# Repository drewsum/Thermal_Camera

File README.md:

# Thermal_Camera
DIY Thermal Camera - Drew Maatman and Michael Laffin

## Hardware:
### KiCad Project:
\Thermal_Camera\rev_a\hdw\Thermal_Camera
Made in KiCad version 8.0.5
PIC32MZ DA Grphics MCU
FLIR Lepton 3.5 Thermal Imagery Sensor
PIC32MZ DA is programmed with firmware via PICKIT4 Header (J1501)
PIC32MZ DA can be held in reset by pressing SW1501 or by inserting jumper across J1502
USB Hub can be reset by pressing SW2501
SPI FLASH can be programmed via J2002

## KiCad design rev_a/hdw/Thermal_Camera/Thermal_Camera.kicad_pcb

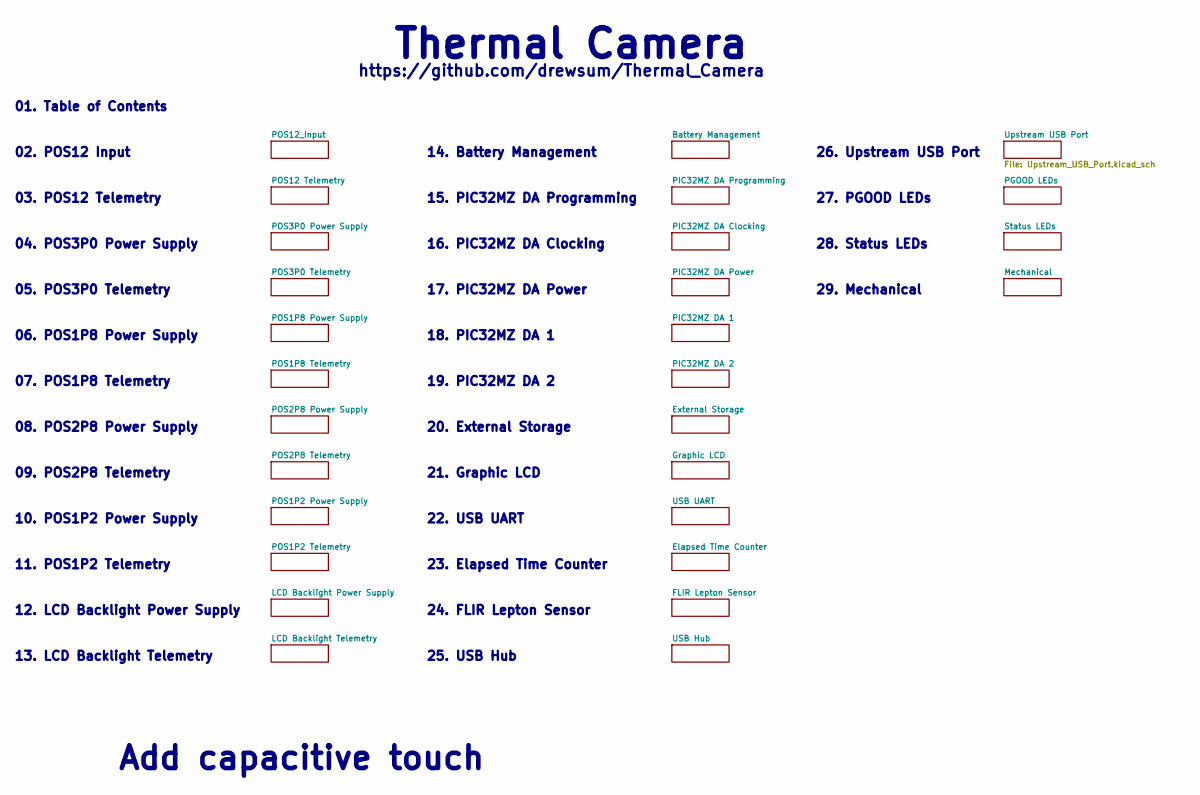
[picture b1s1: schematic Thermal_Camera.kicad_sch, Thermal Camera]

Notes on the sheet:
08. POS2P8 Power Supply
12. LCD Backlight Power Supply
26. Upstream USB Port
15. PIC32MZ DA Programming
28. Status LEDs
05. POS3P0 Telemetry
27. PGOOD LEDs
02. POS12 Input
25. USB Hub
22. USB UART
01. Table of Contents
23. Elapsed Time Counter
20. External Storage
Thermal Camera
24. FLIR Lepton Sensor
11. POS1P2 Telemetry
18. PIC32MZ DA 1
03. POS12 Telemetry
13. LCD Backlight Telemetry
19. PIC32MZ DA 2
14. Battery Management
10. POS1P2 Power Supply
Add capacitive touch
17. PIC32MZ DA Power
https://github.com/drewsum/Thermal_Camera
29. Mechanical
09. POS2P8 Telemetry
07. POS1P8 Telemetry
04. POS3P0 Power Supply
16. PIC32MZ DA Clocking
06. POS1P8 Power Supply
21. Graphic LCD

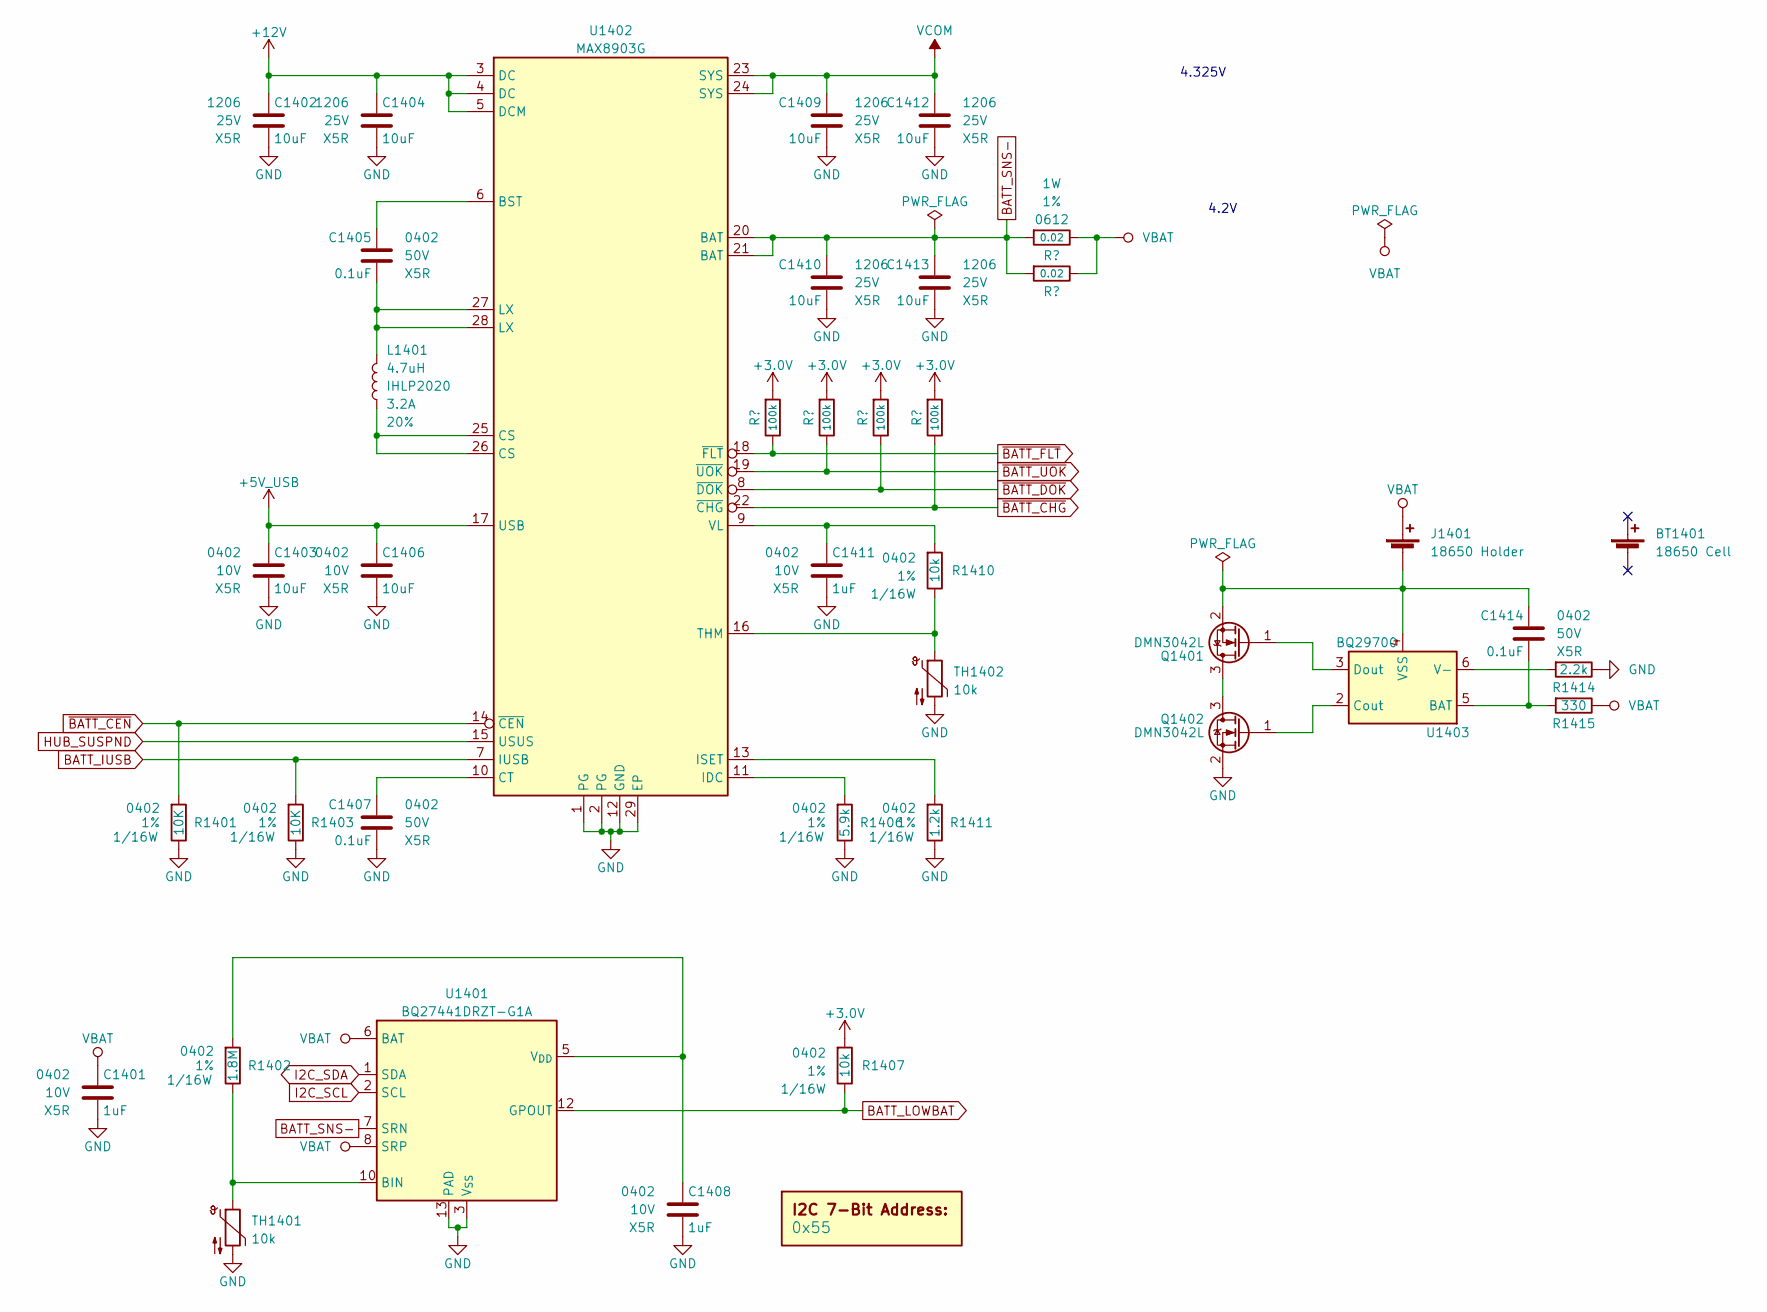
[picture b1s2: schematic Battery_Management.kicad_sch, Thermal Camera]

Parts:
BT1401: 18650 Cell; Digi-Key PN 1568-1488-ND
C1401, C1408, C1411: 1uF; C_0402; Voltage 10V; Digi-Key PN 311-1439-1-ND
C1402, C1404, C1409, C1410, C1412, C1413: 10uF; C_1206; Voltage 25V; Digi-Key PN 399-8153-1-ND
C1403, C1406: 10uF; C_0402; Voltage 10V; Digi-Key PN 490-GRM155R61A106ME11DCT-ND
C1405, C1407, C1414: 0.1uF; C_0402; Voltage 50V; Digi-Key PN 490-10697-1-ND
DOC1401: 0x55
J1401: 18650 Holder; BatteryHolder_MPD_BH-18650-PC2; Digi-Key PN BK-18650-PC2-ND
L1401: 4.7uH; L_Vishay_IHLP-2020; Tolerance 20%; Digi-Key PN 541-1222-1-ND
Q1401, Q1402: DMN3042L; SOT-23; Digi-Key PN DMN3042L-7DICT-ND
R1401, R1403: 10K; R_0402; Tolerance 1%; Digi-Key PN RMCF0402FT10K0CT-ND
R1402: 1.8M; R_0402; Tolerance 1%; Digi-Key PN RMCF0402FT1M80CT-ND
R1404, R1405, R1408, R1409: 100k; R_0402; Tolerance 1%; Digi-Key PN RMCF0402FT100KCT-ND
R1406: 5.9k; R_0402; Tolerance 1%; Digi-Key PN RMCF0402FT5K90CT-ND
R1407, R1410: 10k; R_0402; Tolerance 1%; Digi-Key PN RMCF0402FT10K0CT-ND
R1411: 1.2k; R_0402; Tolerance 1%; Digi-Key PN RMCF0402FT1K20CT-ND
R1412, R1413: 0.02; R_0612; Tolerance 1%; Digi-Key PN P16010CT-ND
R1414: 2.2k; R_0402; Tolerance 1%; Digi-Key PN RMCF0402FT2K20CT-ND
R1415: 330; R_0402; Tolerance 1%; Digi-Key PN RMCF0402FT330RCT-ND
TH1401, TH1402: 10k; R_0402; Digi-Key PN 445-174911-1-ND
U1401: BQ27441DRZT-G1A; Texas_S-PDSO-N12; Digi-Key PN 296-37271-1-ND
U1402: MAX8903G; QFN-28-1EP_4x4mm_P0.4mm_EP2.6x2.6mm; Digi-Key PN MAX8903GETI+-ND
U1403: BQ29700; WSON-6_1.5x1.5mm_P0.5mm; Digi-Key PN 296-43985-1-ND

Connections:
+3.0V: R1404.1, R1405.1, R1407.1, R1408.1, R1409.1; also elsewhere on the board
+5V_USB: C1403.1, C1406.1, U1402.17 (USB); also elsewhere on the board
+12V: C1402.1, C1404.1, U1402.3 (DC), U1402.4 (DC), U1402.5 (DCM); also elsewhere on the board
BATT_IUSB: R1403.1, U1402.7 (IUSB); also elsewhere on the board
BATT_LOWBAT: R1407.2, U1401.12 (GPOUT); also elsewhere on the board
BATT_SNS-: C1410.1, C1413.1, R1412.1, R1413.1, U1401.7 (SRN), U1402.20 (BAT), U1402.21 (BAT)
GND: C1401.2, C1402.2, C1403.2, C1404.2, C1406.2, C1407.2, C1408.2, C1409.2, C1410.2, C1411.2, C1412.2, C1413.2, Q1402.2 (S), R1401.2, R1403.2, R1406.2, R1411.2, R1414.2, TH1401.2, TH1402.2, U1401.3 (V_{SS}), U1401.13 (PAD), U1402.1 (PG), U1402.2 (PG), U1402.12 (GND), U1402.29 (EP); also elsewhere on the board
HUB_SUSPND: U1402.15 (USUS); also elsewhere on the board
I2C_SCL: U1401.2 (SCL); also elsewhere on the board
I2C_SDA: U1401.1 (SDA); also elsewhere on the board
unnamed: C1405.2, L1401.2, U1402.27 (LX), U1402.28 (LX)
unnamed: C1414.1, J1401.2 (-), Q1401.2 (S), U1403.4 (VSS)
unnamed: L1401.1, U1402.25 (CS), U1402.26 (CS)
unnamed: Q1401.3 (D), Q1402.3 (D)
unnamed: Q1401.1 (G), U1403.3 (Dout)
unnamed: Q1402.1 (G), U1403.2 (Cout)
unnamed: R1402.2, TH1401.1, U1401.10 (BIN)
unnamed: C1408.1, R1402.1, U1401.5 (V_{DD})
unnamed: C1405.1, U1402.6 (BST)
unnamed: C1407.1, U1402.10 (CT)
unnamed: R1406.1, U1402.11 (IDC)
unnamed: R1411.1, U1402.13 (ISET)
unnamed: R1410.2, TH1402.1, U1402.16 (THM)
unnamed: C1411.1, R1410.1, U1402.9 (VL)
unnamed: C1414.2, R1415.1, U1403.5 (BAT)
unnamed: R1414.1, U1403.6 (V-)
VBAT: C1401.1, J1401.1 (+), R1412.2, R1413.2, R1415.2, U1401.6 (BAT), U1401.8 (SRP)
VCOM: C1409.1, C1412.1, U1402.23 (SYS), U1402.24 (SYS); also elsewhere on the board
~BATT_CEN: R1401.1, U1402.14 (~CEN); also elsewhere on the board
~BATT_CHG: R1409.2, U1402.22 (~CHG); also elsewhere on the board
~BATT_DOK: R1408.2, U1402.8 (~DOK); also elsewhere on the board
~BATT_FLT: R1404.2, U1402.18 (~FLT); also elsewhere on the board
~BATT_UOK: R1405.2, U1402.19 (~UOK); also elsewhere on the board

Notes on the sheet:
4.325V
4.2V

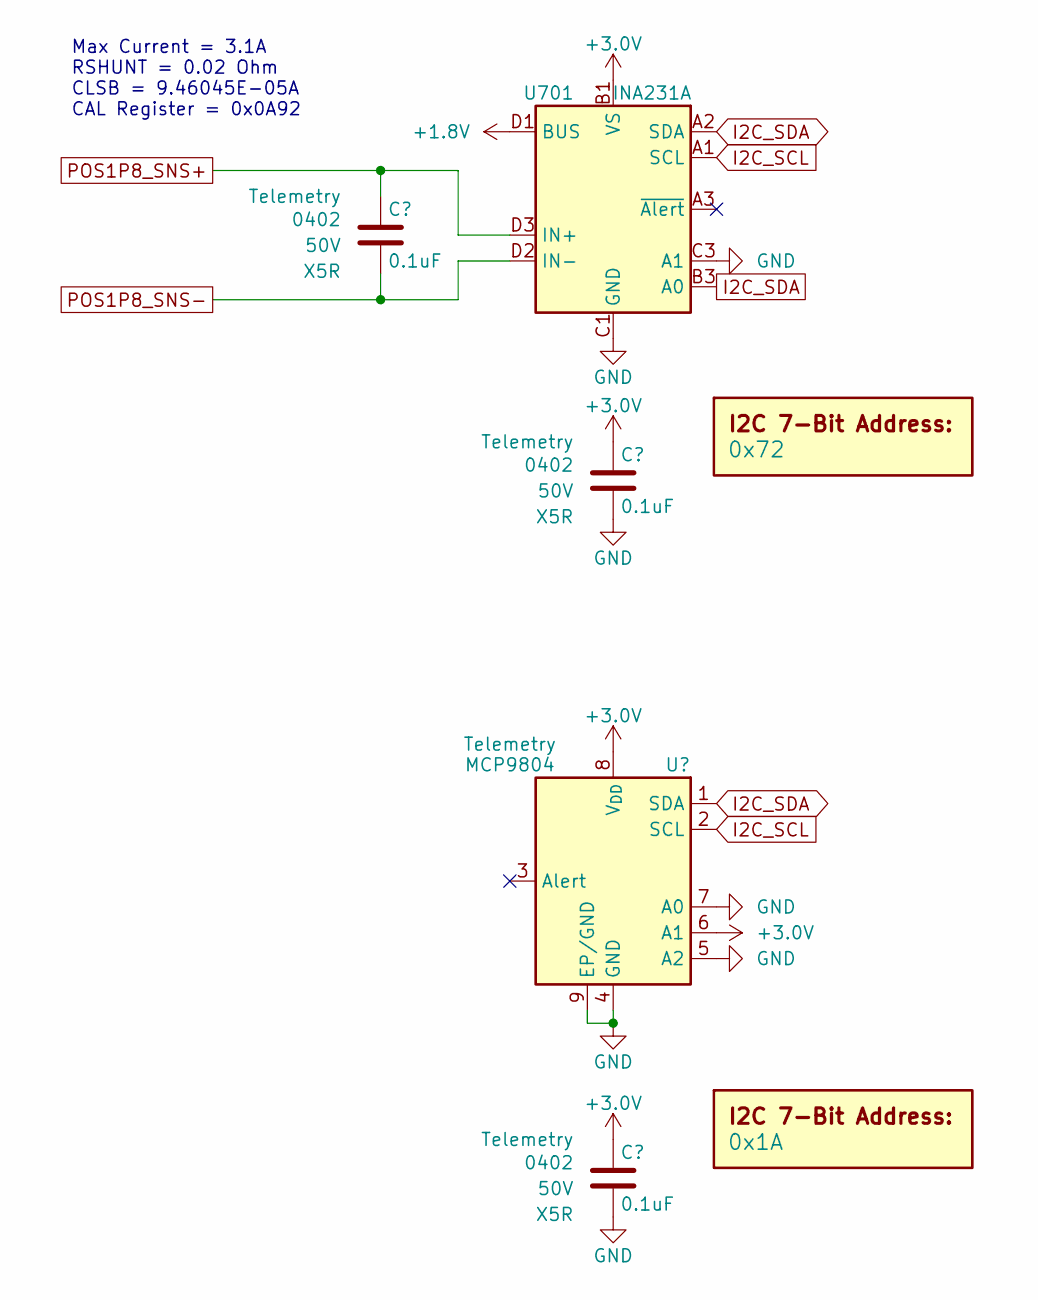
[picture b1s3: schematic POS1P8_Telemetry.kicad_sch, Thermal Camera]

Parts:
C701, C702, C703: 0.1uF; C_0402; Voltage 50V; Digi-Key PN 490-10697-1-ND
DOC701: 0x72
DOC702: 0x1A
U701: INA231A; Texas_DSBGA-12_1.65x1.39mm_Layout3x4_P0.4mm; Digi-Key PN 296-41263-1-ND
U702: MCP9804; DFN-8-1EP_3x2mm_P0.5mm_EP1.3x1.5mm; Digi-Key PN MCP9804T-E/MCCT-ND

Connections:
+1.8V: U701.D1 (BUS); also elsewhere on the board
+3.0V: C702.1, C703.1, U701.B1 (VS), U702.6 (A1), U702.8 (V_{DD}); also elsewhere on the board
GND: C702.2, C703.2, U701.C1 (GND), U701.C3 (A1), U702.4 (GND), U702.5 (A2), U702.7 (A0), U702.9 (EP/GND); also elsewhere on the board
I2C_SCL: U701.A1 (SCL), U702.2 (SCL); also elsewhere on the board
I2C_SDA: U701.A2 (SDA), U701.B3 (A0), U702.1 (SDA); also elsewhere on the board
POS1P8_SNS+: C701.1, U701.D3 (IN+); also elsewhere on the board
POS1P8_SNS-: C701.2, U701.D2 (IN-); also elsewhere on the board

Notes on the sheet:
Max Current = 3.1A RSHUNT = 0.02 Ohm CLSB = 9.46045E-05A CAL Register = 0x0A92

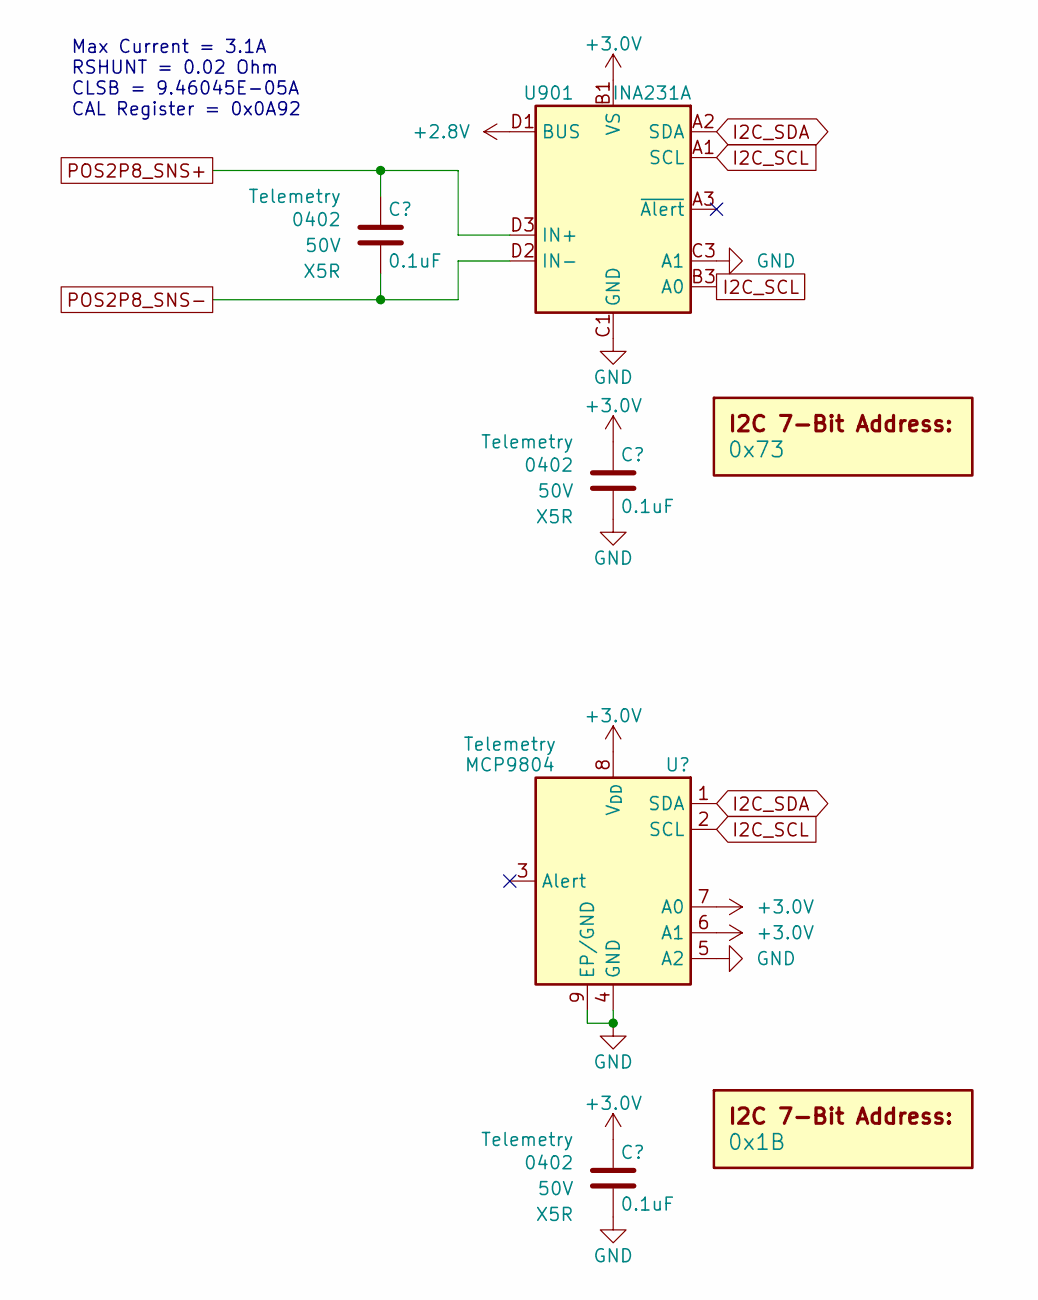
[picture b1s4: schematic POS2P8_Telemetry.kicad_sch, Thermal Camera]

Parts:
C901, C902, C903: 0.1uF; C_0402; Voltage 50V; Digi-Key PN 490-10697-1-ND
DOC901: 0x73
DOC902: 0x1B
U901: INA231A; Texas_DSBGA-12_1.65x1.39mm_Layout3x4_P0.4mm; Digi-Key PN 296-41263-1-ND
U902: MCP9804; DFN-8-1EP_3x2mm_P0.5mm_EP1.3x1.5mm; Digi-Key PN MCP9804T-E/MCCT-ND

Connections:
+2.8V: U901.D1 (BUS); also elsewhere on the board
+3.0V: C902.1, C903.1, U901.B1 (VS), U902.6 (A1), U902.7 (A0), U902.8 (V_{DD}); also elsewhere on the board
GND: C902.2, C903.2, U901.C1 (GND), U901.C3 (A1), U902.4 (GND), U902.5 (A2), U902.9 (EP/GND); also elsewhere on the board
I2C_SCL: U901.A1 (SCL), U901.B3 (A0), U902.2 (SCL); also elsewhere on the board
I2C_SDA: U901.A2 (SDA), U902.1 (SDA); also elsewhere on the board
POS2P8_SNS+: C901.1, U901.D3 (IN+); also elsewhere on the board
POS2P8_SNS-: C901.2, U901.D2 (IN-); also elsewhere on the board

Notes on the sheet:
Max Current = 3.1A RSHUNT = 0.02 Ohm CLSB = 9.46045E-05A CAL Register = 0x0A92

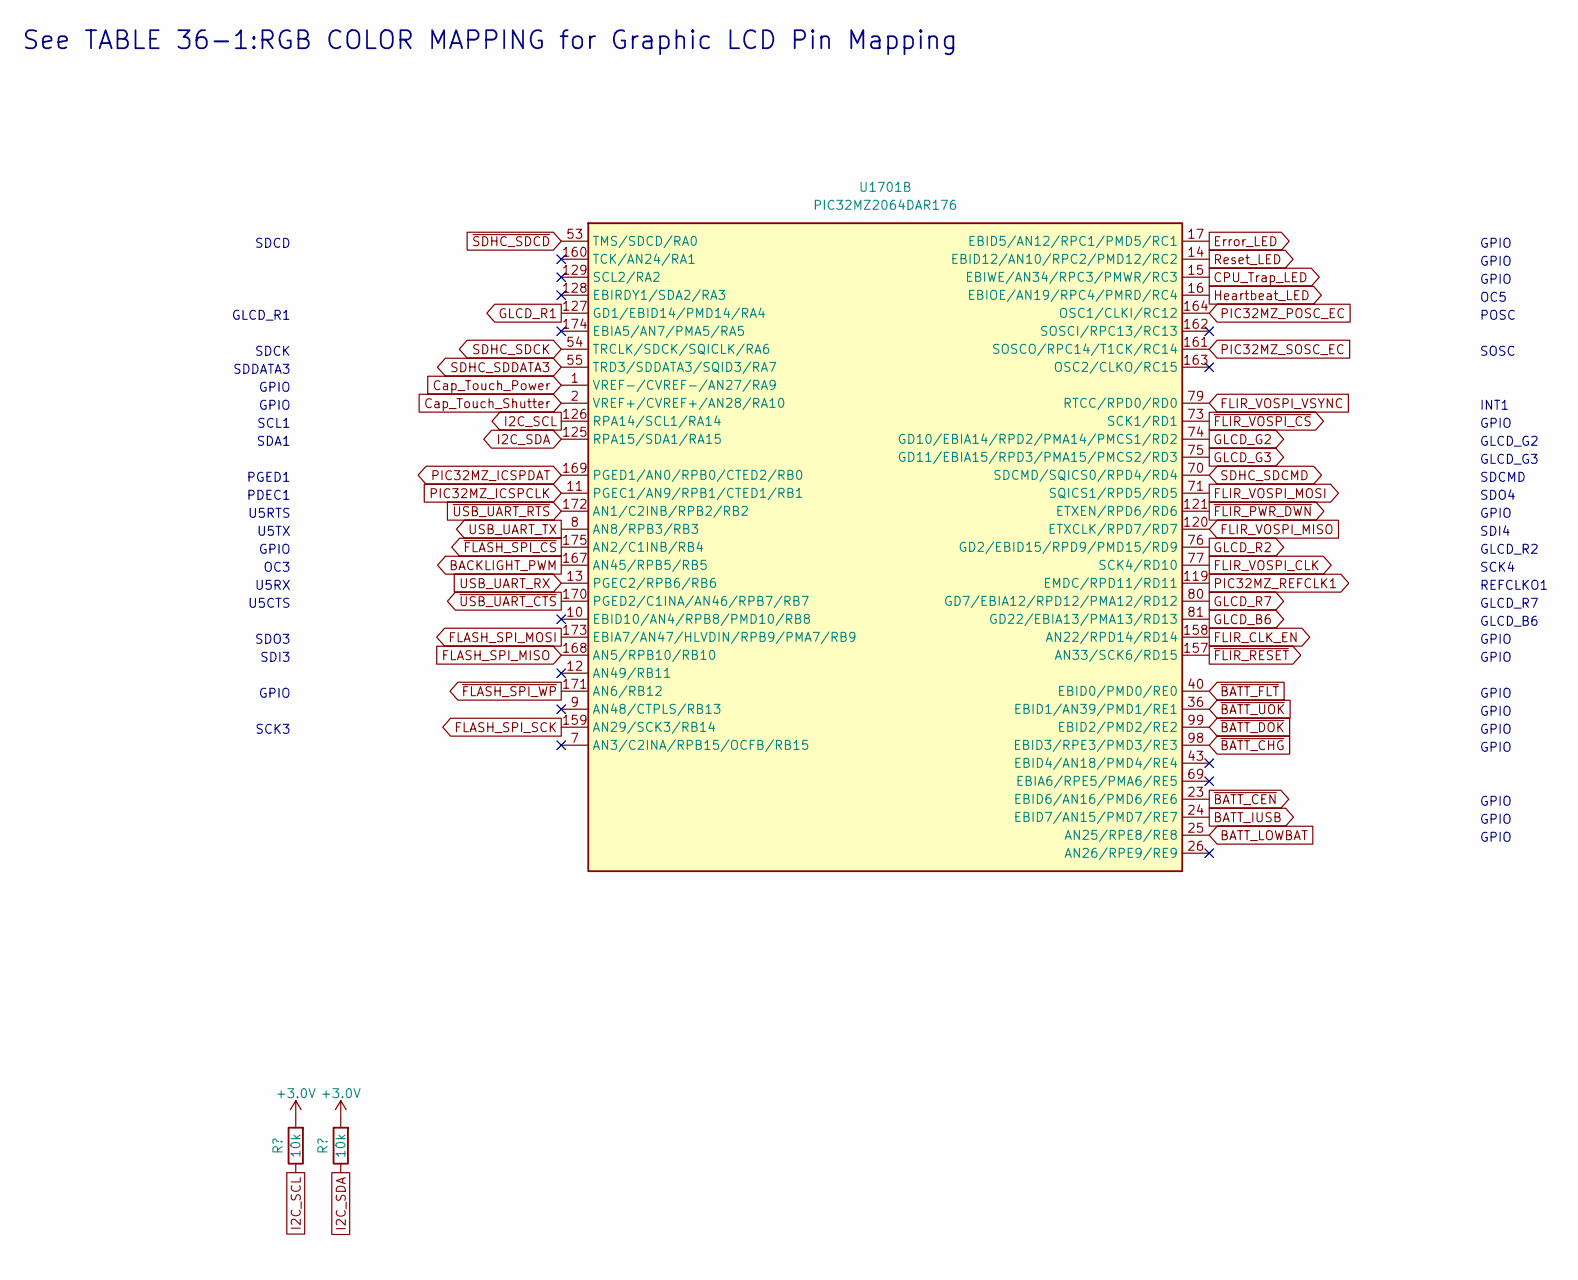
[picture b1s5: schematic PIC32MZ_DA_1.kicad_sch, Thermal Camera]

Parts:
R1801, R1802: 10k; R_0402; Tolerance 1%; Digi-Key PN RMCF0402FT10K0CT-ND
U1701: PIC32MZ2064DAR176; LQFP-176_20x20mm_P0.4mm_7p9x7p9mm_EP; Digi-Key PN PIC32MZ2064DAR176-I/2J-ND

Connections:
+3.0V: R1801.1, R1802.1; also elsewhere on the board
BACKLIGHT_PWM: U1701.167 (AN45/RPB5/RB5); also elsewhere on the board
BATT_IUSB: U1701.24 (EBID7/AN15/PMD7/RE7); also elsewhere on the board
BATT_LOWBAT: U1701.25 (AN25/RPE8/RE8); also elsewhere on the board
CPU_Trap_LED: U1701.15 (EBIWE/AN34/RPC3/PMWR/RC3); also elsewhere on the board
Cap_Touch_Power: U1701.1 (VREF-/CVREF-/AN27/RA9); also elsewhere on the board
Cap_Touch_Shutter: U1701.2 (VREF+/CVREF+/AN28/RA10); also elsewhere on the board
Error_LED: U1701.17 (EBID5/AN12/RPC1/PMD5/RC1); also elsewhere on the board
FLASH_SPI_MISO: U1701.168 (AN5/RPB10/RB10); also elsewhere on the board
FLASH_SPI_MOSI: U1701.173 (EBIA7/AN47/HLVDIN/RPB9/PMA7/RB9); also elsewhere on the board
FLASH_SPI_SCK: U1701.159 (AN29/SCK3/RB14); also elsewhere on the board
FLIR_CLK_EN: U1701.158 (AN22/RPD14/RD14); also elsewhere on the board
FLIR_VOSPI_CLK: U1701.77 (SCK4/RD10); also elsewhere on the board
FLIR_VOSPI_MISO: U1701.120 (ETXCLK/RPD7/RD7); also elsewhere on the board
FLIR_VOSPI_MOSI: U1701.71 (SQICS1/RPD5/RD5); also elsewhere on the board
FLIR_VOSPI_VSYNC: U1701.79 (RTCC/RPD0/RD0); also elsewhere on the board
GLCD_B6: U1701.81 (GD22/EBIA13/PMA13/RD13); also elsewhere on the board
GLCD_G2: U1701.74 (GD10/EBIA14/RPD2/PMA14/PMCS1/RD2); also elsewhere on the board
GLCD_G3: U1701.75 (GD11/EBIA15/RPD3/PMA15/PMCS2/RD3); also elsewhere on the board
GLCD_R1: U1701.127 (GD1/EBID14/PMD14/RA4); also elsewhere on the board
GLCD_R2: U1701.76 (GD2/EBID15/RPD9/PMD15/RD9); also elsewhere on the board
GLCD_R7: U1701.80 (GD7/EBIA12/RPD12/PMA12/RD12); also elsewhere on the board
Heartbeat_LED: U1701.16 (EBIOE/AN19/RPC4/PMRD/RC4); also elsewhere on the board
I2C_SCL: R1801.2, U1701.126 (RPA14/SCL1/RA14); also elsewhere on the board
I2C_SDA: R1802.2, U1701.125 (RPA15/SDA1/RA15); also elsewhere on the board
PIC32MZ_ICSPCLK: U1701.11 (PGEC1/AN9/RPB1/CTED1/RB1); also elsewhere on the board
PIC32MZ_ICSPDAT: U1701.169 (PGED1/AN0/RPB0/CTED2/RB0); also elsewhere on the board
PIC32MZ_POSC_EC: U1701.164 (OSC1/CLKI/RC12); also elsewhere on the board
PIC32MZ_REFCLK1: U1701.119 (EMDC/RPD11/RD11); also elsewhere on the board
PIC32MZ_SOSC_EC: U1701.161 (SOSCO/RPC14/T1CK/RC14); also elsewhere on the board
Reset_LED: U1701.14 (EBID12/AN10/RPC2/PMD12/RC2); also elsewhere on the board
SDHC_SDCK: U1701.54 (TRCLK/SDCK/SQICLK/RA6); also elsewhere on the board
SDHC_SDCMD: U1701.70 (SDCMD/SQICS0/RPD4/RD4); also elsewhere on the board
SDHC_SDDATA3: U1701.55 (TRD3/SDDATA3/SQID3/RA7); also elsewhere on the board
USB_UART_RX: U1701.13 (PGEC2/RPB6/RB6); also elsewhere on the board
USB_UART_TX: U1701.8 (AN8/RPB3/RB3); also elsewhere on the board
~BATT_CEN: U1701.23 (EBID6/AN16/PMD6/RE6); also elsewhere on the board
~BATT_CHG: U1701.98 (EBID3/RPE3/PMD3/RE3); also elsewhere on the board
~BATT_DOK: U1701.99 (EBID2/PMD2/RE2); also elsewhere on the board
~BATT_FLT: U1701.40 (EBID0/PMD0/RE0); also elsewhere on the board
~BATT_UOK: U1701.36 (EBID1/AN39/PMD1/RE1); also elsewhere on the board
~FLASH_SPI_CS: U1701.175 (AN2/C1INB/RB4); also elsewhere on the board
~FLASH_SPI_WP: U1701.171 (AN6/RB12); also elsewhere on the board
~FLIR_PWR_DWN: U1701.121 (ETXEN/RPD6/RD6); also elsewhere on the board
~FLIR_RESET: U1701.157 (AN33/SCK6/RD15); also elsewhere on the board
~FLIR_VOSPI_CS: U1701.73 (SCK1/RD1); also elsewhere on the board
~SDHC_SDCD: U1701.53 (TMS/SDCD/RA0); also elsewhere on the board
~USB_UART_CTS: U1701.170 (PGED2/C1INA/AN46/RPB7/RB7); also elsewhere on the board
~USB_UART_RTS: U1701.172 (AN1/C2INB/RPB2/RB2); also elsewhere on the board

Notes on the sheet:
PGED1
POSC
GPIO
U5TX
U5CTS
SCK4
SDCMD
OC5
SOSC
SDO3
SDCK
SCL1
OC3
GLCD_G3
GLCD_B6
SDI3
REFCLKO1
U5RTS
U5RX
SDI4
SDDATA3
INT1
GLCD_R2
GLCD_G2
PDEC1
SDCD
GLCD_R7
SDO4
GLCD_R1
SCK3
SDA1
See TABLE 36-1:RGB COLOR MAPPING for Graphic LCD Pin Mapping

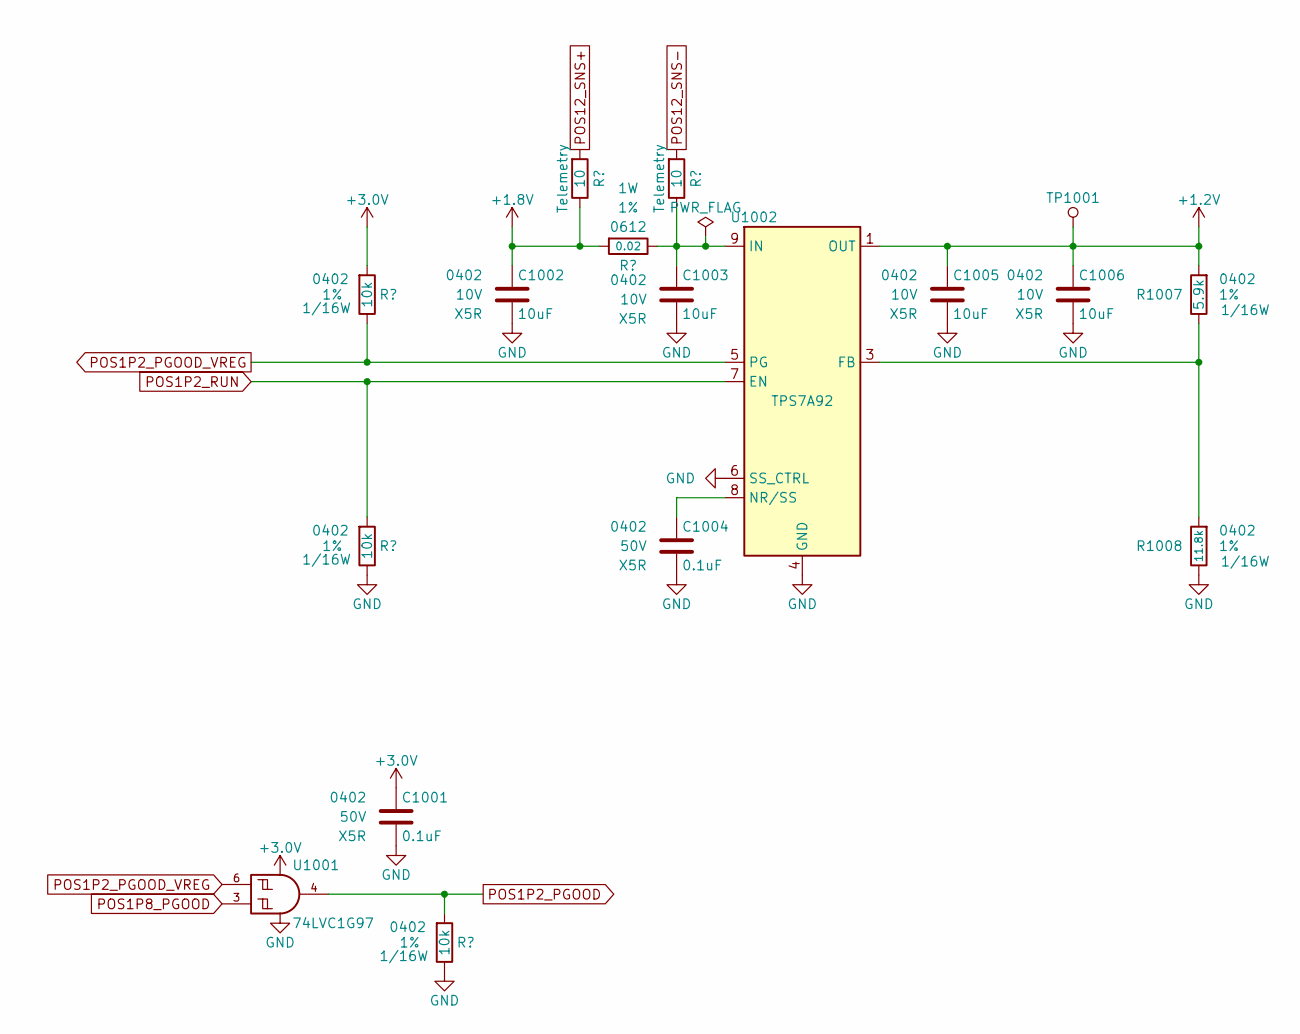
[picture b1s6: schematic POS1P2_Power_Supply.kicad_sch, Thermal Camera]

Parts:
C1001, C1004: 0.1uF; C_0402; Voltage 50V; Digi-Key PN 490-10697-1-ND
C1002, C1003, C1005, C1006: 10uF; C_0402; Voltage 10V; Digi-Key PN 490-GRM155R61A106ME11DCT-ND
R1001, R1002, R1003: 10k; R_0402; Tolerance 1%; Digi-Key PN RMCF0402FT10K0CT-ND
R1004, R1006: 10; R_0402; Tolerance 1%; Digi-Key PN RMCF0402FT10R0CT-ND
R1005: 0.02; R_0612; Tolerance 1%; Digi-Key PN P16010CT-ND
R1007: 5.9k; R_0402; Tolerance 1%; Digi-Key PN RMCF0402FT5K90CT-ND
R1008: 11.8k; R_0402; Tolerance 1%; Digi-Key PN RMCF0402FT11K8CT-ND
TP1001: TP; Test_Point
U1001: 74LVC1G97; SOT-363_SC-70-6; Digi-Key PN 296-15582-1-ND
U1002: TPS7A92; Texas_S-PDSO-N10_EP1.2x2mm; Digi-Key PN TPS7A9201DSKR

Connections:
+1.2V: C1005.1, C1006.1, R1007.1, TP1001.1 (TP), U1002.1 (OUT), U1002.2 (OUT); also elsewhere on the board
+1.8V: C1002.1, R1004.2, R1005.1; also elsewhere on the board
+3.0V: C1001.1, R1001.1, U1001.5 (VCC); also elsewhere on the board
GND: C1001.2, C1002.2, C1003.2, C1004.2, C1005.2, C1006.2, R1002.2, R1003.2, R1008.2, U1001.1 (GND), U1001.2 (GND), U1002.4 (GND), U1002.6 (SS_CTRL), U1002.11 (GND); also elsewhere on the board
unnamed: C1003.1, R1005.2, R1006.2, U1002.9 (IN), U1002.10 (IN)
unnamed: R1007.2, R1008.1, U1002.3 (FB)
unnamed: C1004.1, U1002.8 (NR/SS)
POS1P2_PGOOD: R1003.1, U1001.4; also elsewhere on the board
POS1P2_PGOOD_VREG: R1001.2, U1001.6, U1002.5 (PG)
POS1P2_RUN: R1002.1, U1002.7 (EN); also elsewhere on the board
POS1P8_PGOOD: U1001.3; also elsewhere on the board
POS12_SNS+: R1004.1; also elsewhere on the board
POS12_SNS-: R1006.1; also elsewhere on the board

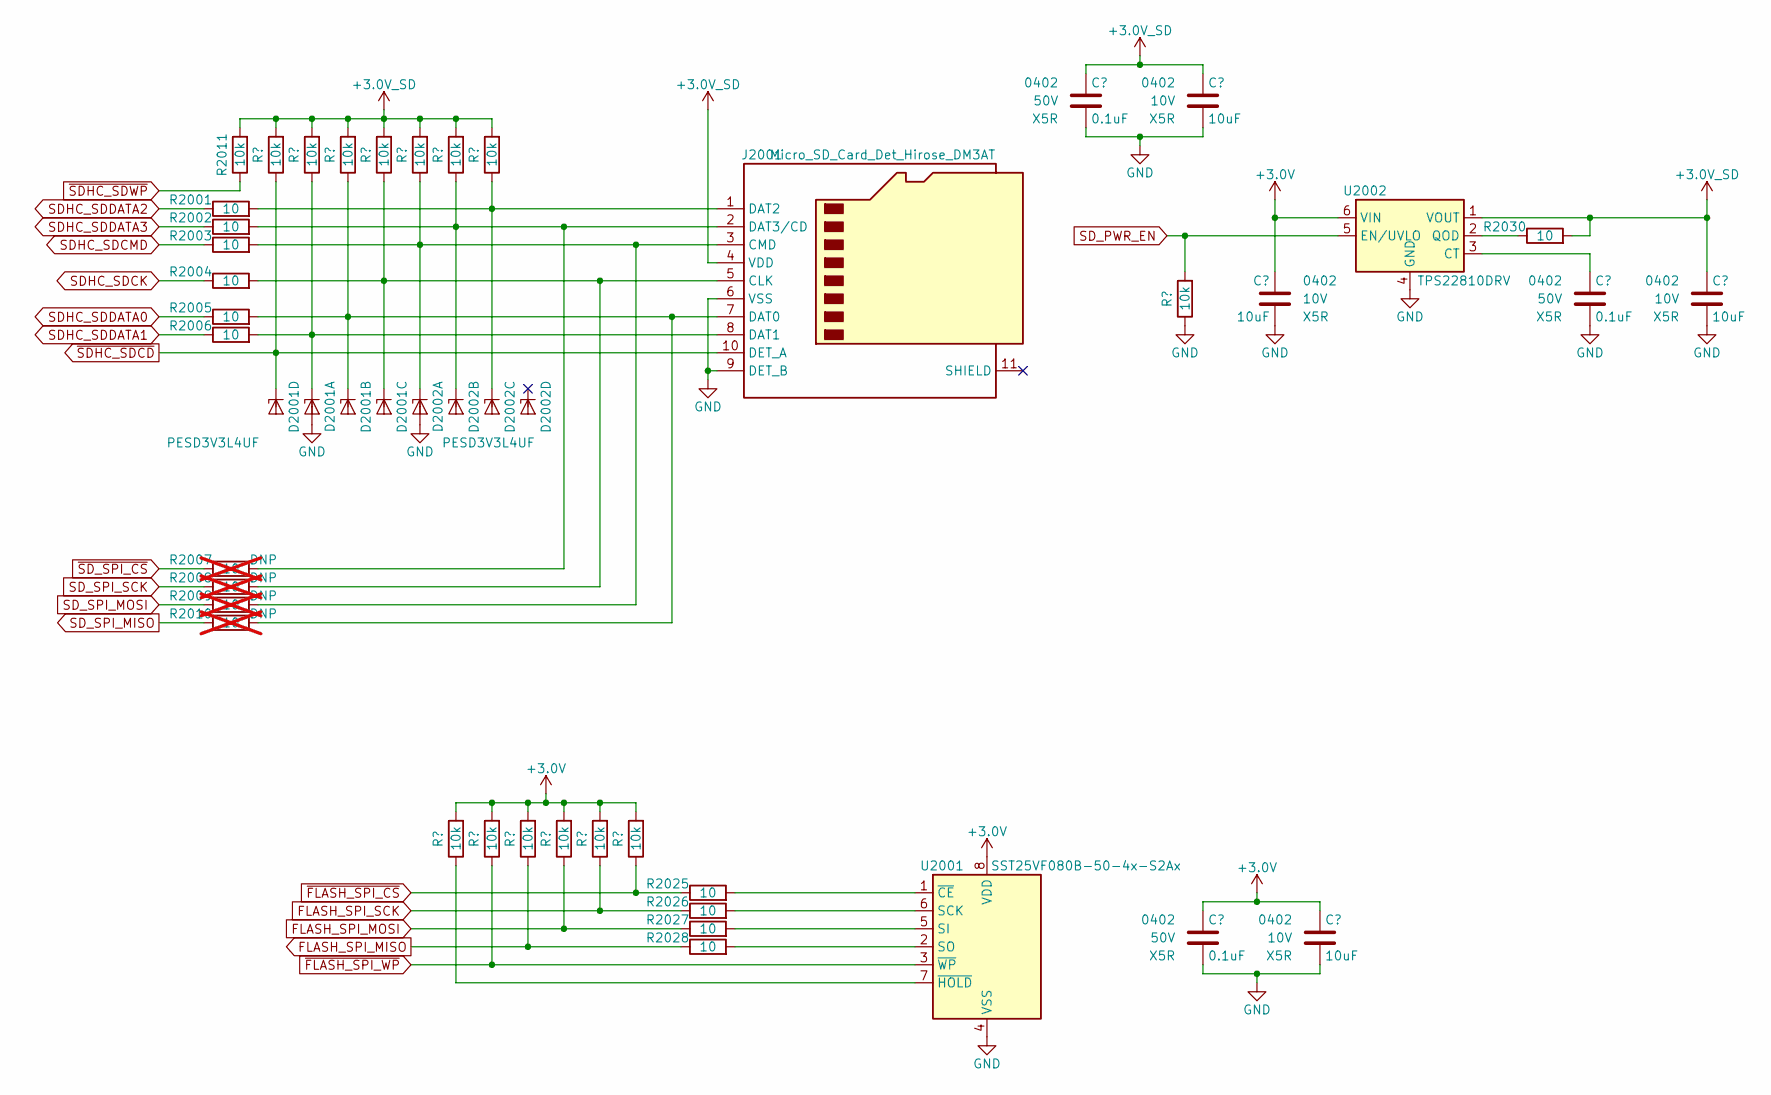
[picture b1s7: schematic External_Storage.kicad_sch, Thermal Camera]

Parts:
C2001, C2003, C2006: 0.1uF; C_0402; Voltage 50V; Digi-Key PN 490-10697-1-ND
C2002, C2004, C2005, C2007: 10uF; C_0402; Voltage 10V; Digi-Key PN 490-GRM155R61A106ME11DCT-ND
D2001, D2002: PESD3V3L4UF; SOT-886
J2001: Micro_SD_Card_Det_Hirose_DM3AT; Hirose_DM3AT-SF-PEJM5; Digi-Key PN HR1964CT-ND
R2001, R2002, R2003, R2004, R2005, R2006, R2025, R2026, R2027, R2028, R2030: 10; R_0402; Tolerance 1%; Digi-Key PN RMCF0402FT10R0CT-ND
R2007, R2008, R2009, R2010: 10; R_0402; Tolerance 1%; Digi-Key PN RMCF0402FT10R0CT-ND; not fitted
R2011, R2012, R2013, R2014, R2015, R2016, R2017, R2018, R2019, R2020, R2021, R2022, R2023, R2024, R2029: 10k; R_0402; Tolerance 1%; Digi-Key PN RMCF0402FT10K0CT-ND
U2001: SST25VF080B-50-4x-S2Ax; SOIC-8_5.275x5.275mm_P1.27mm; Digi-Key PN SST25VF080B-50-4C-S2AF-ND
U2002: TPS22810DRV; WSON-6-1EP_2x2mm_P0.65mm_EP1x1.6mm; Digi-Key PN 296-47868-1-ND

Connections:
+3.0V: C2003.1, C2004.1, C2005.1, R2018.1, R2020.1, R2021.1, R2022.1, R2023.1, R2024.1, U2001.8 (VDD), U2002.6 (VIN); also elsewhere on the board
+3.0V_SD: C2001.1, C2002.1, C2007.1, J2001.4 (VDD), R2011.1, R2012.1, R2013.1, R2014.1, R2015.1, R2016.1, R2017.1, R2019.1, R2030.1, U2002.1 (VOUT)
FLASH_SPI_MISO: R2021.2, R2028.2; also elsewhere on the board
FLASH_SPI_MOSI: R2022.2, R2027.2; also elsewhere on the board
FLASH_SPI_SCK: R2023.2, R2026.2; also elsewhere on the board
GND: C2001.2, C2002.2, C2003.2, C2004.2, C2005.2, C2006.2, C2007.2, D2001.2 (A), D2001.5 (A), D2002.2 (A), D2002.5 (A), J2001.6 (VSS), J2001.9 (DET_B), R2029.2, U2001.4 (VSS), U2002.4 (GND), U2002.7 (GND); also elsewhere on the board
unnamed: D2001.1 (K1), J2001.8 (DAT1), R2006.1, R2013.2
unnamed: D2001.3 (K2), J2001.7 (DAT0), R2005.1, R2010.1, R2014.2
unnamed: D2001.4 (K3), J2001.5 (CLK), R2004.1, R2008.1, R2015.2
unnamed: D2002.1 (K1), J2001.3 (CMD), R2003.1, R2009.1, R2016.2
unnamed: D2002.3 (K2), J2001.2 (DAT3/CD), R2002.1, R2007.1, R2017.2
unnamed: D2002.4 (K3), J2001.1 (DAT2), R2001.1, R2019.2
unnamed: R2026.1, U2001.6 (SCK)
unnamed: R2027.1, U2001.5 (SI)
unnamed: R2028.1, U2001.2 (SO)
unnamed: R2025.1, U2001.1 (~CE)
unnamed: R2018.2, U2001.7 (~HOLD)
unnamed: C2006.1, U2002.3 (CT)
unnamed: R2030.2, U2002.2 (QOD)
SDHC_SDCK: R2004.2; also elsewhere on the board
SDHC_SDCMD: R2003.2; also elsewhere on the board
SDHC_SDDATA0: R2005.2; also elsewhere on the board
SDHC_SDDATA1: R2006.2; also elsewhere on the board
SDHC_SDDATA2: R2001.2; also elsewhere on the board
SDHC_SDDATA3: R2002.2; also elsewhere on the board
SD_PWR_EN: R2029.1, U2002.5 (EN/UVLO); also elsewhere on the board
SD_SPI_MISO: R2010.2; also elsewhere on the board
SD_SPI_MOSI: R2009.2; also elsewhere on the board
SD_SPI_SCK: R2008.2; also elsewhere on the board
~FLASH_SPI_CS: R2024.2, R2025.2; also elsewhere on the board
~FLASH_SPI_WP: R2020.2, U2001.3 (~WP); also elsewhere on the board
~SDHC_SDCD: D2001.6 (K4), J2001.10 (DET_A), R2012.2; also elsewhere on the board
~SDHC_SDWP: R2011.2; also elsewhere on the board
~SD_SPI_CS: R2007.2; also elsewhere on the board
